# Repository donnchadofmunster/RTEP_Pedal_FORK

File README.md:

# 🎛️ Real-Time Digital Effects Pedal

> A modular, real-time audio effects system for Raspberry Pi, developed in modern C++ with multithreading, low-latency processing, and unit-tested DSP effect chains.

## 📜 Project Overview

The Real-Time Harmoniser is a standalone real-time embedded system designed to apply audio effects (like pitch-shifting and gain distortion) to incoming audio with minimal latency. The pedal is controllable via a hardware interface and written for the ENG5220: Real-Time Embedded Programming course.

**Key Features:**
- Modular DSP architecture with hot-swappable effect chains
- Sample-by-sample processing for minimal latency
- Real-time capable Harmonizer using [SignalsmithStretch](https://github.com/Signalsmith-Audio/signalsmith-stretch)
- Multithreaded control-safe design with atomic buffer swapping
- CI-integrated Google Test unit testing
- Memory-safe code verified with Valgrind

## 🧩 System Architecture

```
+-----------+     +--------------+     +--------------------+
| Audio In  | --> | Sampling     | --> | DigitalSignalChain | --> Audio Out
+-----------+     +--------------+     +--------------------+
                                       |  Gain, Fuzz, Harmonizer ...
                                       +--------------------+
```

Each audio sample flows through a configurable DSP chain loaded dynamically from a config file.

## ⚙️ Getting Started

### 🔧 Prerequisites

- Raspberry Pi 4/5 (or any Linux system)
- `libsndfile1-dev`, `libasound2-dev`, `libgtest-dev`, `valgrind`
- CMake ≥ 3.7, Clang or GCC

### 🛠️ Build

```bash
chmod +x code/init.sh code/build.sh
./code/init.sh    # Installs dependencies and fetches submodules
./code/build.sh   # Builds the pedal and test binaries
```

### ▶️ Run

```bash
./code/run.sh     # Runs the real-time pedal binary
```

### ✅ Unit Tests

```bash
./code/unit_test.sh    # Runs unit tests with Valgrind
```

### 🧼 Clean

```bash
./code/clean_run.sh     # Re-builds the project and runs
./code/clean_test.sh    # Re-builds the project and runs the integration test
```

## 📂 Project Structure

```
code/
├── src/              # All source files
│   ├── dsp/          # DSP chain and factory
│   ├── effects/      # Harmonizer, Gain, Fuzz etc.
│   ├── sampling/     # Sample and output modules
│   └── test/         # Functional and unit tests
├── assets/           # Input/output WAV files and configs
├── CMakeLists.txt    # Project build configuration
├── run.sh            # Launches the pedal binary
├── test.sh           # Runs Valgrind test harness
└── init.sh           # Dependency setup and submodule fetch
```

## 📊 Performance

| Metric             | Value           |
|--------------------|-----------------|
| Latency (per sample) | < 3μs (tested on x86) |
| Realtime Factor    | ~10x            |
| CPU Usage          | < 40% on RPi 4  |
| Memory Leaks       | ❌ None (Valgrind verified) |

## 🔬 Features Under Development

- Live web-based configuration via Angular UI (`shred.local`)
- Additional effects: Reverb, Delay
- Plugin support for 3rd-party effect modules

## ✅ Achievements

| Criteria                         | Status       |
|----------------------------------|--------------|
| Multithreaded DSP                | ✅ Lock-free atomic switching |
| Realtime sample-by-sample       | ✅ Implemented in Harmonizer |
| Unit Testing                     | ✅ GTest + Valgrind |
| CI/CD Integration                | ✅ GitHub Actions |
| Well-commented, structured code | ✅ Reviewed and documented |
| Pedal UI and Config             | ⚠️ UI In Progress |

## 📜 License

MIT License. See `LICENSE` for details.

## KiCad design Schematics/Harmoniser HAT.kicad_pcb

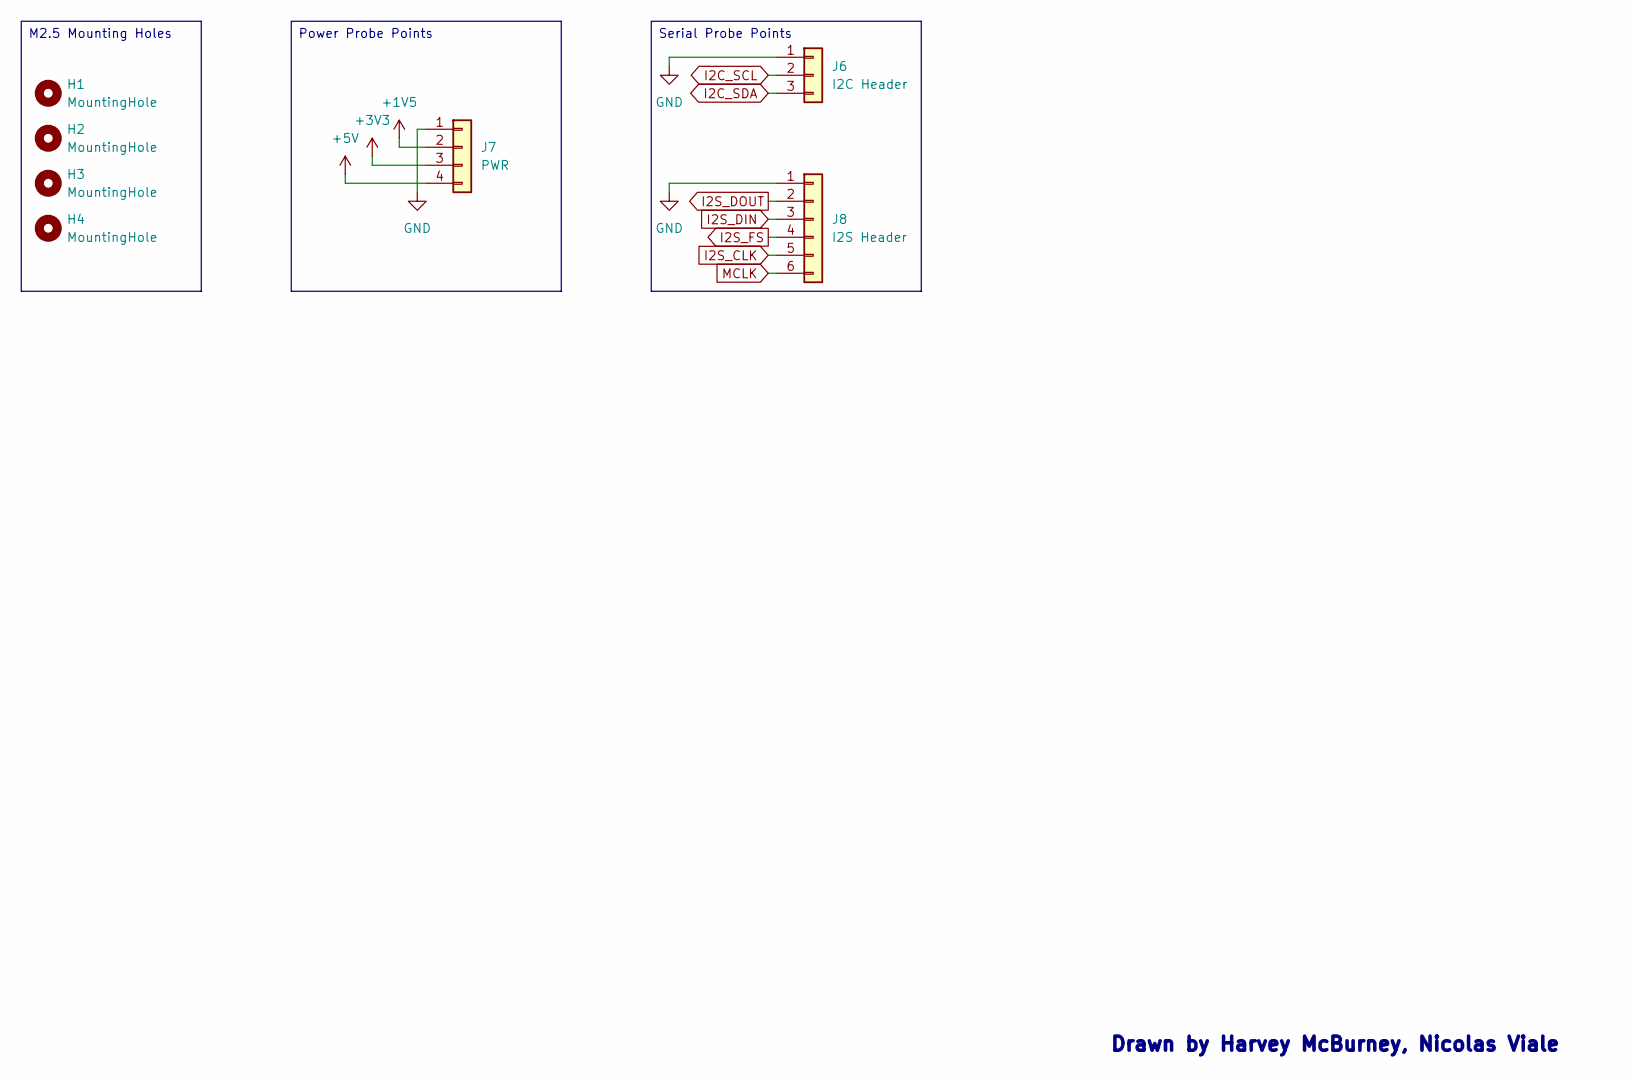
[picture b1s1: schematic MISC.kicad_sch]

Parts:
H1, H2, H3, H4: MountingHole; MountingHole_2.7mm_M2.5
J6: I2C Header; PinHeader_1x03_P2.54mm_Vertical
J7: PWR; PinHeader_1x04_P2.54mm_Vertical
J8: I2S Header; PinHeader_1x06_P2.54mm_Vertical

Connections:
+1V5: J7.2
+3V3: J7.3; also elsewhere on the board
+5V: J7.4; also elsewhere on the board
GND: J6.1, J7.1, J8.1; also elsewhere on the board
I2C_SCL: J6.2; also elsewhere on the board
I2C_SDA: J6.3; also elsewhere on the board
I2S_CLK: J8.5; also elsewhere on the board
I2S_DIN: J8.3; also elsewhere on the board
I2S_DOUT: J8.2; also elsewhere on the board
I2S_FS: J8.4; also elsewhere on the board
MCLK: J8.6

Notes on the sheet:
Drawn by Harvey McBurney, Nicolas Viale
M2.5 Mounting Holes
Serial Probe Points
Power Probe Points

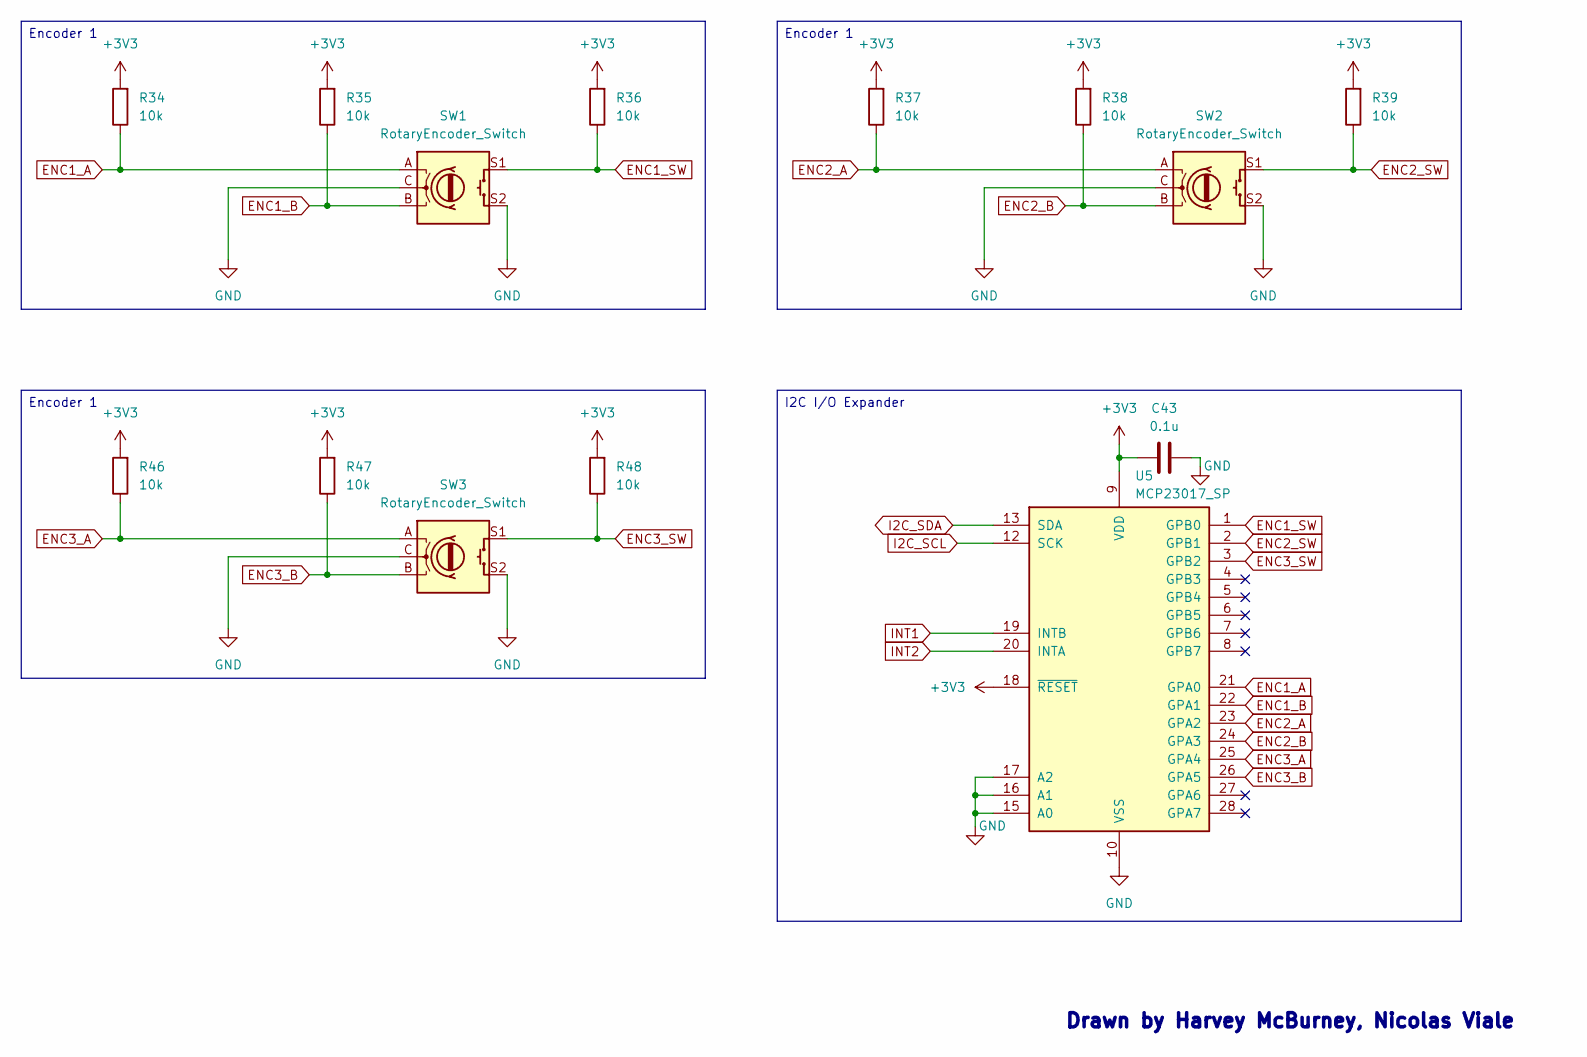
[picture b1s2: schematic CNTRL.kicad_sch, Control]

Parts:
C43: 0.1u; C_Disc_D4.7mm_W2.5mm_P5.00mm
R34, R35, R36, R37, R38, R39, R46, R47, R48: 10k; R_Axial_DIN0207_L6.3mm_D2.5mm_P10.16mm_Horizontal
SW1, SW2, SW3: RotaryEncoder_Switch; RotaryEncoder_Bourns_Vertical_PEC12R-3x17F-Sxxxx
U5: MCP23017_SP; DIP-28_W7.62mm

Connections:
+3V3: C43.2, R34.2, R35.2, R36.2, R37.2, R38.2, R39.2, R46.2, R47.2, R48.2, U5.9 (VDD), U5.18 (~RESET); also elsewhere on the board
ENC1_A: R34.1, SW1.A, U5.21 (GPA0)
ENC1_B: R35.1, SW1.B, U5.22 (GPA1)
ENC1_SW: R36.1, SW1.S1, U5.1 (GPB0)
ENC2_A: R37.1, SW2.A, U5.23 (GPA2)
ENC2_B: R38.1, SW2.B, U5.24 (GPA3)
ENC2_SW: R39.1, SW2.S1, U5.2 (GPB1)
ENC3_A: R46.1, SW3.A, U5.25 (GPA4)
ENC3_B: R47.1, SW3.B, U5.26 (GPA5)
ENC3_SW: R48.1, SW3.S1, U5.3 (GPB2)
GND: C43.1, SW1.C, SW1.S2, SW2.C, SW2.S2, SW3.C, SW3.S2, U5.10 (VSS), U5.15 (A0), U5.16 (A1), U5.17 (A2); also elsewhere on the board
I2C_SCL: U5.12 (SCK); also elsewhere on the board
I2C_SDA: U5.13 (SDA); also elsewhere on the board
INT1: U5.19 (INTB); also elsewhere on the board
INT2: U5.20 (INTA); also elsewhere on the board

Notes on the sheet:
Drawn by Harvey McBurney, Nicolas Viale
I2C I/O Expander
Encoder 1

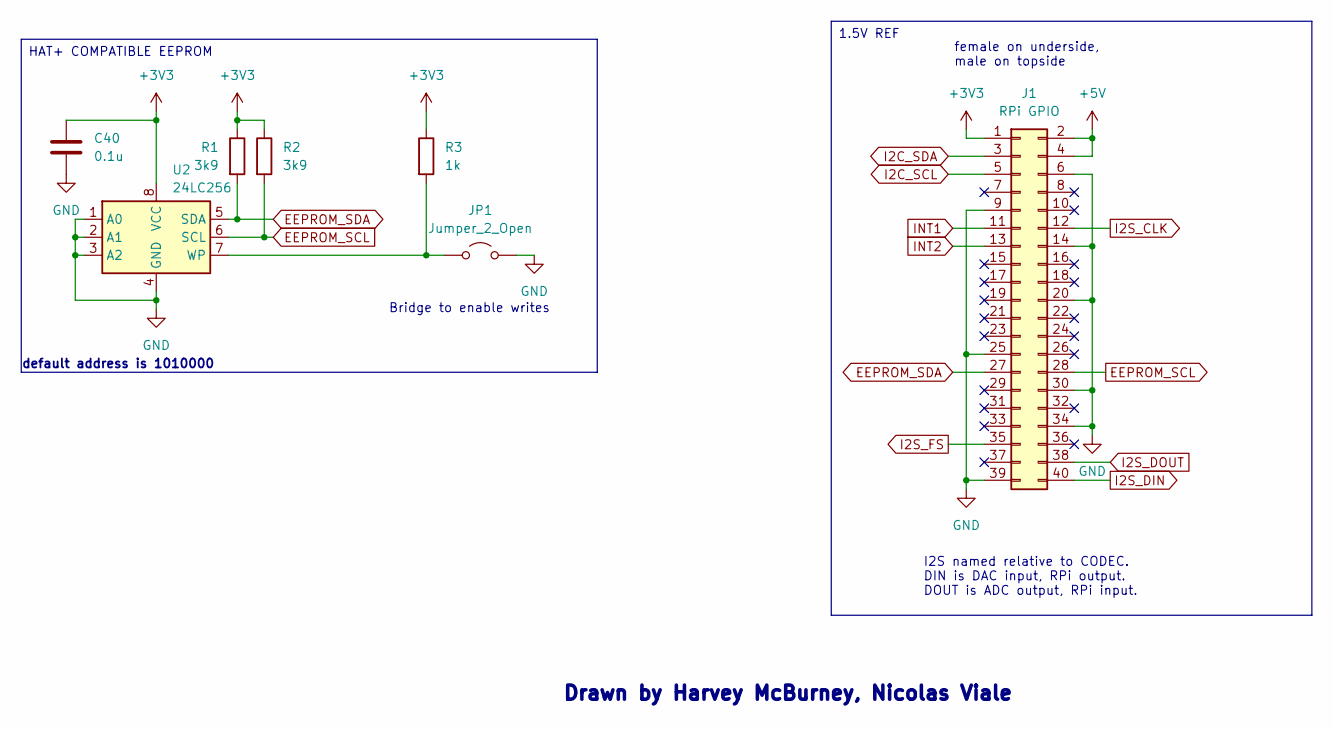
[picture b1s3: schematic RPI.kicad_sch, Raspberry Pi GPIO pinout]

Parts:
C40: 0.1u; C_Disc_D4.7mm_W2.5mm_P5.00mm
J1: RPi GPIO; PinHeader_2x20_P2.54mm_Vertical
JP1: Jumper_2_Open; PinHeader_1x02_P2.54mm_Vertical
R1, R2: 3k9; R_Axial_DIN0207_L6.3mm_D2.5mm_P10.16mm_Horizontal
R3: 1k; R_Axial_DIN0207_L6.3mm_D2.5mm_P10.16mm_Horizontal
U2: 24LC256; SOIC-8_3.9x4.9mm_P1.27mm

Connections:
+3V3: C40.1, J1.1, R1.1, R2.1, R3.1, U2.8 (VCC); also elsewhere on the board
+5V: J1.2, J1.4; also elsewhere on the board
EEPROM_SCL: J1.28, R2.2, U2.6 (SCL)
EEPROM_SDA: J1.27, R1.2, U2.5 (SDA)
GND: C40.2, J1.6, J1.9, J1.14, J1.20, J1.25, J1.30, J1.34, J1.39, JP1.2 (B), U2.1 (A0), U2.2 (A1), U2.3 (A2), U2.4 (GND); also elsewhere on the board
I2C_SCL: J1.5; also elsewhere on the board
I2C_SDA: J1.3; also elsewhere on the board
I2S_CLK: J1.12; also elsewhere on the board
I2S_DIN: J1.40; also elsewhere on the board
I2S_DOUT: J1.38; also elsewhere on the board
I2S_FS: J1.35; also elsewhere on the board
INT1: J1.11; also elsewhere on the board
INT2: J1.13; also elsewhere on the board
unnamed: JP1.1 (A), R3.2, U2.7 (WP)

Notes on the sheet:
Drawn by Harvey McBurney, Nicolas Viale
female on underside, male on topside
default address is 1010000
I2S named relative to CODEC. DIN is DAC input, RPi output. DOUT is ADC output, RPi input.
Bridge to enable writes
HAT+ COMPATIBLE EEPROM
1.5V REF

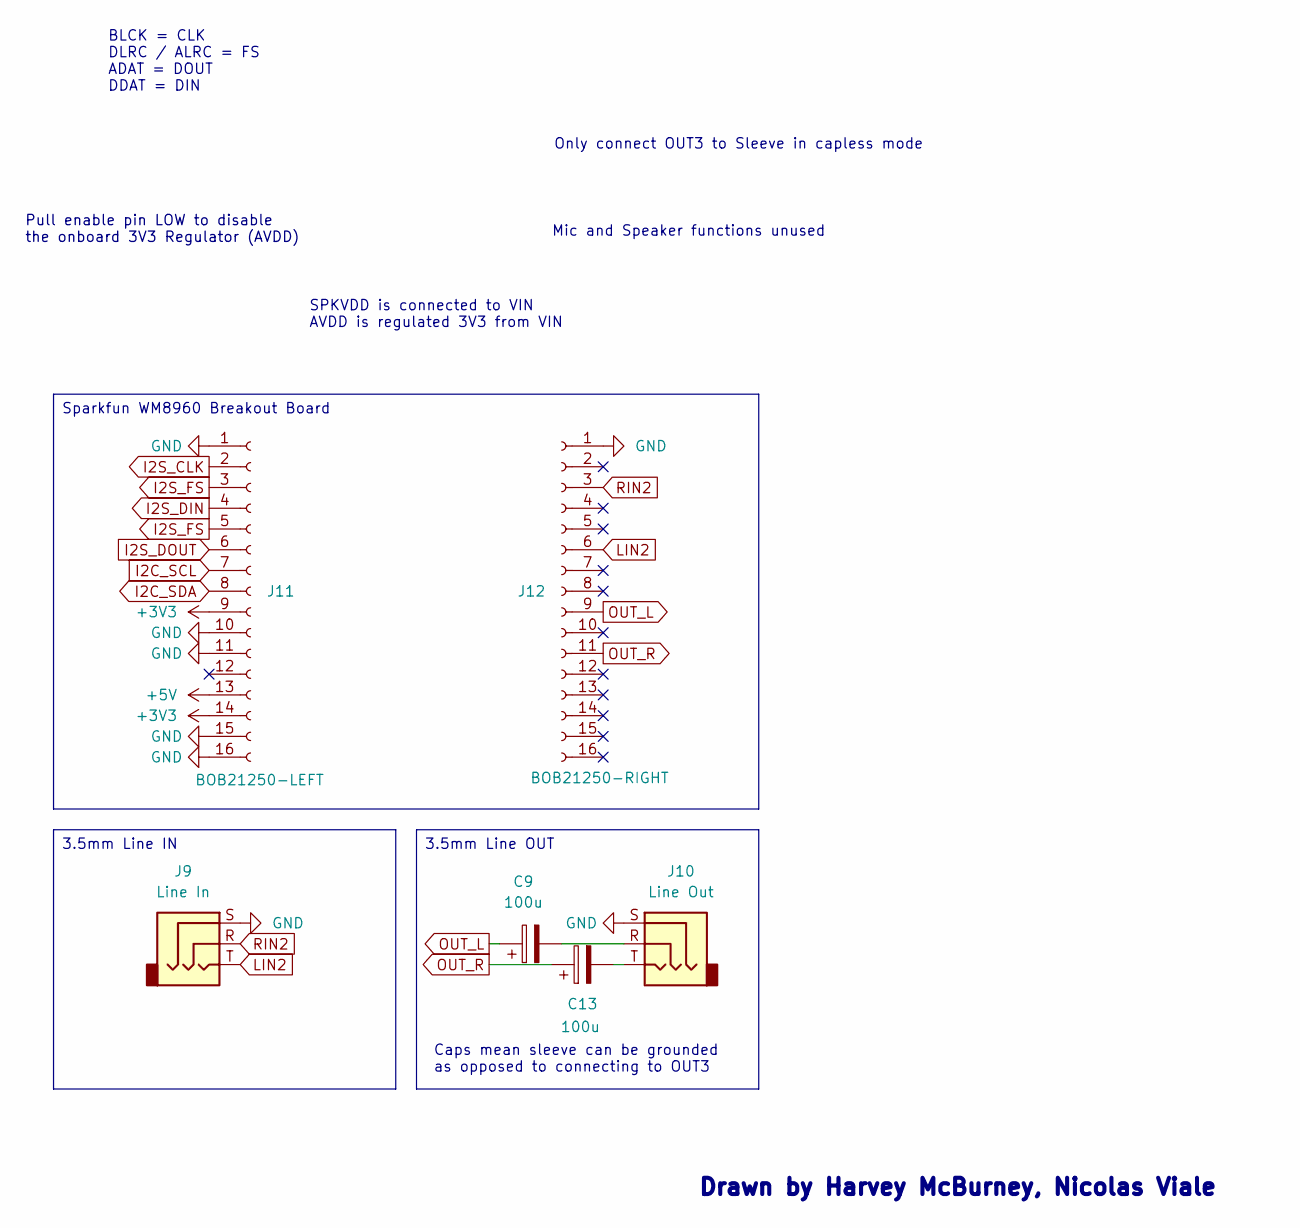
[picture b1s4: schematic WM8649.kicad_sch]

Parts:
C9, C13: 100u; CP_Radial_D8.0mm_P5.00mm
J9: Line In; Jack_3.5mm_CUI_SJ1-3523N_Horizontal
J10: Line Out; Jack_3.5mm_CUI_SJ1-3523N_Horizontal
J11: BOB21250-LEFT; PinSocket_1x16_P2.54mm_Vertical
J12: BOB21250-RIGHT; PinSocket_1x16_P2.54mm_Vertical

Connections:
+3V3: J11.9, J11.14; also elsewhere on the board
+5V: J11.13; also elsewhere on the board
GND: J9.S, J10.S, J11.1, J11.10, J11.11, J11.15, J11.16, J12.1; also elsewhere on the board
I2C_SCL: J11.7; also elsewhere on the board
I2C_SDA: J11.8; also elsewhere on the board
I2S_CLK: J11.2; also elsewhere on the board
I2S_DIN: J11.4; also elsewhere on the board
I2S_DOUT: J11.6; also elsewhere on the board
I2S_FS: J11.3, J11.5; also elsewhere on the board
LIN2: J9.T, J12.6
unnamed: C9.2, J10.R
unnamed: C13.2, J10.T
RIN2: J9.R, J12.3

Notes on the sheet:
Only connect OUT3 to Sleeve in capless mode
Mic and Speaker functions unused
Caps mean sleeve can be grounded as opposed to connecting to OUT3
BLCK = CLK DLRC / ALRC = FS ADAT = DOUT DDAT = DIN
SPKVDD is connected to VIN AVDD is regulated 3V3 from VIN
Drawn by Harvey McBurney, Nicolas Viale
Pull enable pin LOW to disable the onboard 3V3 Regulator (AVDD)
3.5mm Line IN
Sparkfun WM8960 Breakout Board
3.5mm Line OUT

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
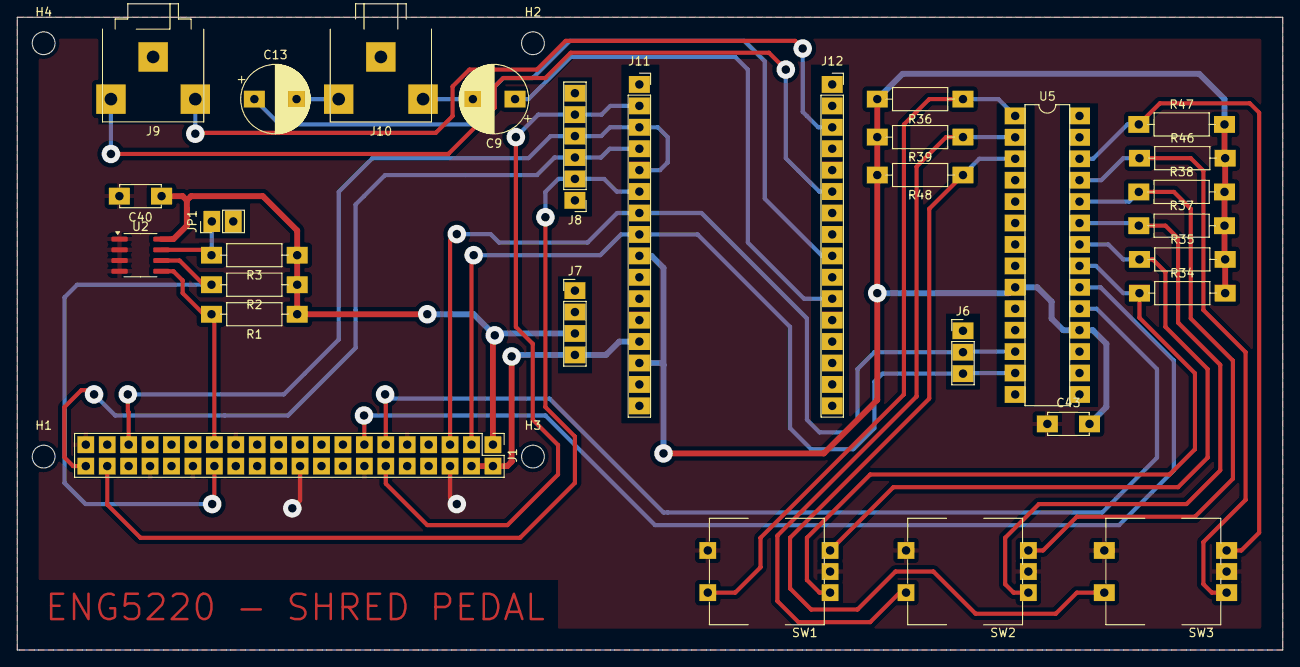
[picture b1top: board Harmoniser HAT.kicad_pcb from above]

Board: 2 copper layers, 150.0 x 75.0 mm, 34 parts (0 on the bottom side), 29 nets.

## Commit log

2025-02-08 Initial Schematic Commit
    Pinout of GPIO and CODEC. Added Four Rotary Encoders. Still to do power, audio in and out.
2025-02-09 Added recommended op-amps
    Added recommended op-amps (without values) with dual mono TS in and out
2025-02-12 Input Buffer & EEPROM
    line and instrument level buffers for the input added. EEPROM added and credits attributed !
2025-02-12 trying to delete this useless file
2025-02-12 FOUND HOW TO!
2025-02-17 Added report template, synced to overleaf
2025-02-19 code diagram added
2025-02-20 Schematic Update
    Added EEPROM connections
2025-02-20 Added I/O Expander
    I/O Expander added, 4 spare pins, still need to decouple.
    Fixed some references to 3.3V, now all 3V3.
2025-02-21 Added Debug Headers
    Added debug headers for I2C, I2S, and power. Also added m2.5 mounting holes for hat
2025-02-22 Started adding footprints, changed values.
    Added footprints for most components. need to check in uni which sizes are available and what will need to be ordered from mouser.
    Changed line in/out to TRS as this will be more reliable and added 0 ohm resistor options to bypass mono input and use line in/out as stereo.
2025-02-23 Updated to KiCAD v9
2025-02-25 Initial code classes and initialisations
2025-02-25 Setup CMake, build script and run script
2025-02-25 Added all footprints, updated PCB
    Added footprints using uni available components where possible. Might be necessary to change op-amps as they are large and not made for audio. PCB has a mockup of component placements but probably ne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
2025-02-26 initial samplingmodule implementation
2025-02-26 samplingmodule comments
2025-02-26 Adjusted Capacitor Footprints
2025-02-26 Changed footprints, added 3d model to GPIO
2025-02-26 added BOM
2025-02-27 slight gitignore change
2025-02-27 made build more stable
2025-02-27 mre build stuff
2025-02-27 mock sampler (untested)
2025-02-27 Mock sampler working!
2025-02-28 Stereo Mocksampler
2025-02-28 mock output module (untested)
2025-02-28 some comments
2025-03-03 TESTING PACKAGE, (effects untested)
2025-03-05 PCB design start
    started on it :)
2025-03-05 PCB set-up & Jack Sockets
    Added 3D file for the Rpi5 and the 1/4" jack sockets. Finalised the dimensions of the PCB with the Pi HAT hole dimensions.
2025-03-06 sample module
2025-03-10 Merged Pitch Shifting into Main after full test inside Branch
2025-03-10 Added installdependencies script, fixed run and build script, fixed harmonizer and memory tracker imports
2025-03-10 Set audio files to be linked to the assets folder rather than code folder
2025-03-12 Fix for Uni PCB
    CODEC module, DIP package, and through-hole less components
2025-03-12 Finished PCB routing
    New Layout fits perfectly, now all the parts are through-hole and routed together. 20 Vias is a nightmare but better than what we started with
2025-03-12 File labelling
2025-03-13 renamed the PCB
2025-03-15 assembly files
    for the UNI PCB
2025-04-02 assembly files
2025-04-03 new uP AS7341 library
    ISSUE - the spectral data ready bit is never set back high so every code times out and doesn't print
2025-04-07 Reformatted before CI/CD
2025-04-09 Added init.sh, made come UX changed
2025-04-09 Added CICD Pipeline
2025-04-09 Updated CICD to V4
2025-04-09 Added sudo to init.sh
2025-04-09 Made CICD go to correct build folder
2025-04-09 Fixed init.sh and added CI/CD for all but testing
2025-04-09 Bitmap files started
2025-04-09 hex files added + key bitmaps
2025-04-09 Key Bitmaps Fully Added
2025-04-09 Harmoniser working for semitone arrays, creating multiple outputs
2025-04-09 Made harmoniser use a semitone array rather than single semitones
2025-04-09 added jpg
2025-04-10 Integrated harmonising into the harmoniser object
2025-04-10 Harmoniser now fully working with harmonies and individual notes
2025-04-10 added effect factory, changed src/cmakelists, builds but untested
2025-04-11 Fixed memory issues with Memory Tracker
2025-04-11 FIXED IT ALL, TESTING OVERHAUL, MEMORY TRACKER REFACTOR, ADDED OCTAVE
2025-04-11 MORE EFFECTS
2025-04-12 Added setting to effects
2025-04-12 REAL TIME HARMONISER HELL YEA
2025-04-12 Docs and optimisation
2025-04-12 BIG REORG
2025-04-12 new unit tests
2025-04-12 Update ci.yml, added unit tests
2025-04-14 ci changes
2025-04-14 ci test
2025-04-14 trying signalsmith as a submodule
2025-04-14 changed apt to apt get,
2025-04-14 added threads and callbacks to DSC
2025-04-14 refactoring
2025-04-14 the tinies most annoying CI fix
2025-04-14 more CI fixes
2025-04-15 Added guitar input and output using ALSA - Minimal latency
2025-04-15 Fixed broken CMake Files - Wrong project name used
2025-04-15 Added images folder for inclusion in wiki
    includes images of PCB with labels for components and headers
2025-04-16 added submodules
2025-04-16 Implimented signal chain with live guitar input
2025-04-16 Real time Harmoniser now working with Guitar Input
2025-04-16 cmakelists cleanup
2025-04-16 Added polyphonic functionality for Harmoniser
2025-04-16 Deleted now obselete memory tracker
2025-04-17 Added HW "flowcharts"
2025-04-17 Added oscilloscope images from CODEC
2025-04-17 Initial commit
    DisplayDriver and supporting files
2025-04-17 Tidied up Schematic
2025-04-17 added config
2025-04-17 Fixed power connections on CODEC
    So the codec board regulates its own AVDD which we had named but disconnected. In order for this regulation to happen the EN pin must be pulled high (not low as it says in the documentation).
    SPKVDD was also disconnected as by default this is taken from VIN (5V) anyway, this means the CODEC boards don't need to be modified anymore.
    Still need to test these on the board if time allows.
2025-04-17 Fixed left and right output channels
2025-04-18 CONFIG BABY
2025-04-18 got rid of latex, added readme
2025-04-18 update redme
2025-04-18 Added SPI/I2C/I2S enabling to init.sh
    Haven't checked this on the pi but should work. If someone could test this by disabling these parameters in config.txt that would be great :)
2025-04-18 Created EEPROM Settings
    Created EEPROM settings, still need to make device tree overlay (https://www.raspberrypi.com/documentation/computers/configuration.html#device-trees-overlays-and-parameters)
2025-04-18 added audioIO module
2025-04-18 Change SPI and I2C command to "0" from "1" to enable.
2025-04-18 Revert signalsmith-stretch
2025-04-18 re-upload of init.sh
2025-04-18 added code diagram
2025-04-19 Encoder Input & Handler
    IMPORTANT:
    - the test code hasn't been pushed, I will aim to do that later
    - right now the handler prints to the terminal, all that is needed is to uncomment the UI handler calls once that handler has been implemented.
2025-04-19 Created overlay for custom PCB
    Not sure if this will work, worth testing when we get a chance as this will be uploaded to the EEPROM to automatically configure i2c, i2s, and GPIO for interrupts.
    Will require building to dtbo before flashing EEPROM.
2025-04-19 Fixed init.sh to install UI drivers
2025-04-19 Updated audio I/O to remove Time Step, and thus reducing guitar latency
2025-04-19 Change DisplayDriver to Display class
    Implement UI Handler to handler encoder input, configuration and display updates
    Update EncoderHandler to call UIHandler
2025-04-19 Update main.cpp
    Add initialisation of encoderhandler and uihandler
2025-04-19 Updated Main to remove timeStep from Sample
2025-04-19 Updated encoder code
2025-04-19 Update UIHandler.cpp
    Add debug statements
2025-04-20 Screen working with encoders
2025-04-20 Fixed issue with semitones not able to go above initial number
2025-04-21 Updated git submodule to older version compatable with the Shred Pedal
2025-04-21 Changed Init to check if Rpi is active to ensure CI/CD compatibility on Git
2025-04-21 Uploaded older version of Signalsmith Stretch to fix build on CI/CD
2025-04-21 Encoder handler chanedd
2025-04-21 Fixed drivers
2025-04-21 CI_BUILD
2025-04-21 Added libsnd1
2025-04-21 Updated YML
